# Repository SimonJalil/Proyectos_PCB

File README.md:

# Proyectos_PCB
En este repositorio se encuentran algunos proyectos relacionados con el diseño de PCB en KICAD

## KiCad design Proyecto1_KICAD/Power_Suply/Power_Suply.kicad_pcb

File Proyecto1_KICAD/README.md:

# Proyecto1_KICAD
Fuente de tension

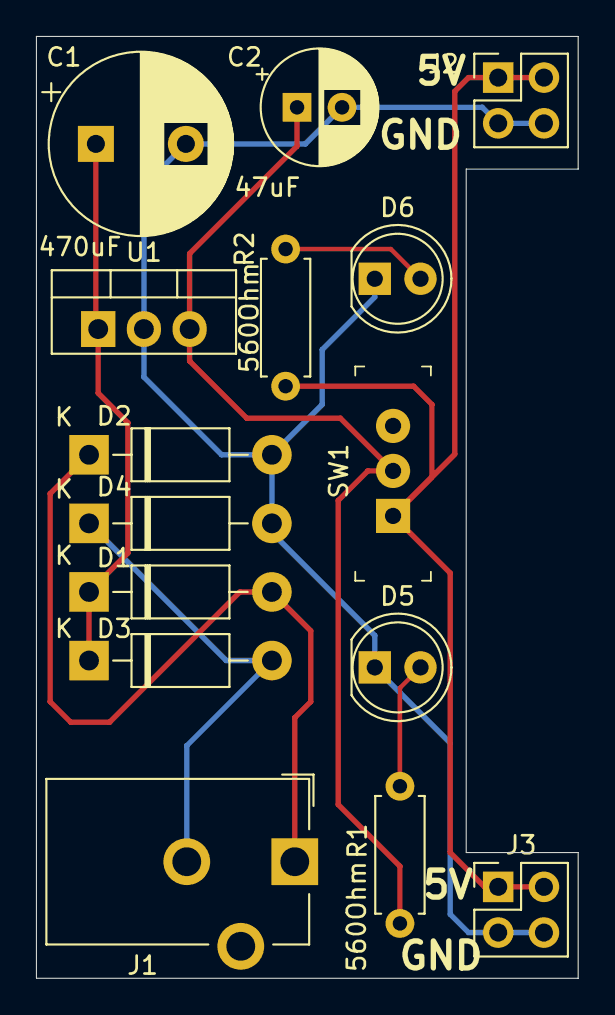
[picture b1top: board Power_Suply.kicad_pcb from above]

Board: 2 copper layers, 30.1 x 52.3 mm, 15 parts (0 on the bottom side), 8 nets.

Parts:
C1: CP; CP_Radial_D10.0mm_P5.00mm
C2: CP; CP_Radial_D6.3mm_P2.50mm
D1, D2, D3, D4: 1N4007; D_DO-41_SOD81_P10.16mm_Horizontal
D5, D6: LED; LED_D5.0mm
J1: Barrel_Jack_Switch; BarrelJack_CUI_PJ-102AH_Horizontal
J2, J3: Conn_02x02_Odd_Even; PinHeader_2x02_P2.54mm_Vertical
R1, R2: R; R_Axial_DIN0207_L6.3mm_D2.5mm_P7.62mm_Horizontal
SW1: SW_DPDT_x2; Switch_Slide_11.6x4mm_EG1218
U1: LM7805_TO220; TO-220-3_Vertical

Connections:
/V-: C1.2, C2.2, D2.2, D4.2, D5.1, D6.1, J2.3, J2.4, J3.3, J3.4, U1.2
/Vin: C1.1, D1.1, D3.1, U1.1
/Vout1: C2.1, R1.1, SW1.2, U1.3
/Vout2: J2.1, J2.2, J3.1, J3.2, R2.1, SW1.1
unnamed: D1.2, D2.1, J1.1
unnamed: D3.2, D4.1, J1.2
unnamed: D5.2, R1.2
unnamed: D6.2, R2.2

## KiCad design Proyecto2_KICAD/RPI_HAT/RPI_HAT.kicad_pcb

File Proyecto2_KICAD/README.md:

# Proyecto2_KICAD
Raspberry Pi HAT

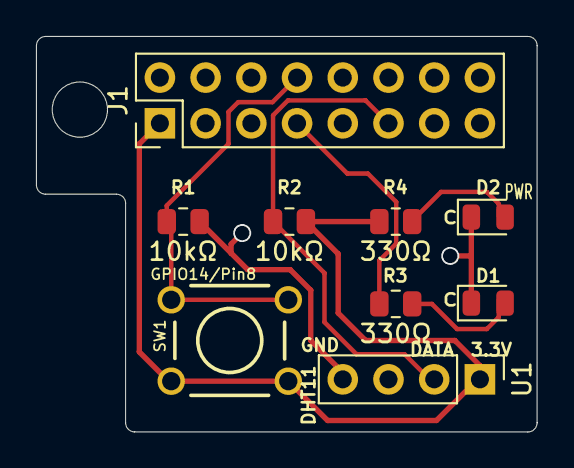
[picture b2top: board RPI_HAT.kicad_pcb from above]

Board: 2 copper layers, 27.8 x 22.0 mm, 9 parts (0 on the bottom side), 7 nets.

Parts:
D1, D2: LED; LED_0805_2012Metric
J1: Raspberry_Pi_2_3; PinHeader_2x08_P2.54mm_Vertical
R1, R2: 10kΩ; R_0805_2012Metric
R3, R4: 330Ω; R_0805_2012Metric
SW1: SW_DPST; SW_PUSHBUTTON_PTH
U1: DHT11; PinHeader_1x04_P2.54mm_Vertical

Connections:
/3V3: J1.1, R2.2, R4.1, SW1.1, U1.1
/button_input: J1.8, R1.1, SW1.2
GND: D1.1, D2.1, J1.6, J1.9, R1.2, U1.4
unnamed: D1.2, R3.2
unnamed: D2.2, R4.2
unnamed: J1.7, R3.1
unnamed: J1.11, R2.1, U1.2

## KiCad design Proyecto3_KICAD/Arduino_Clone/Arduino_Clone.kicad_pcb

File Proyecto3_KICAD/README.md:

# Proyecto3_KICAD
Arduino clone

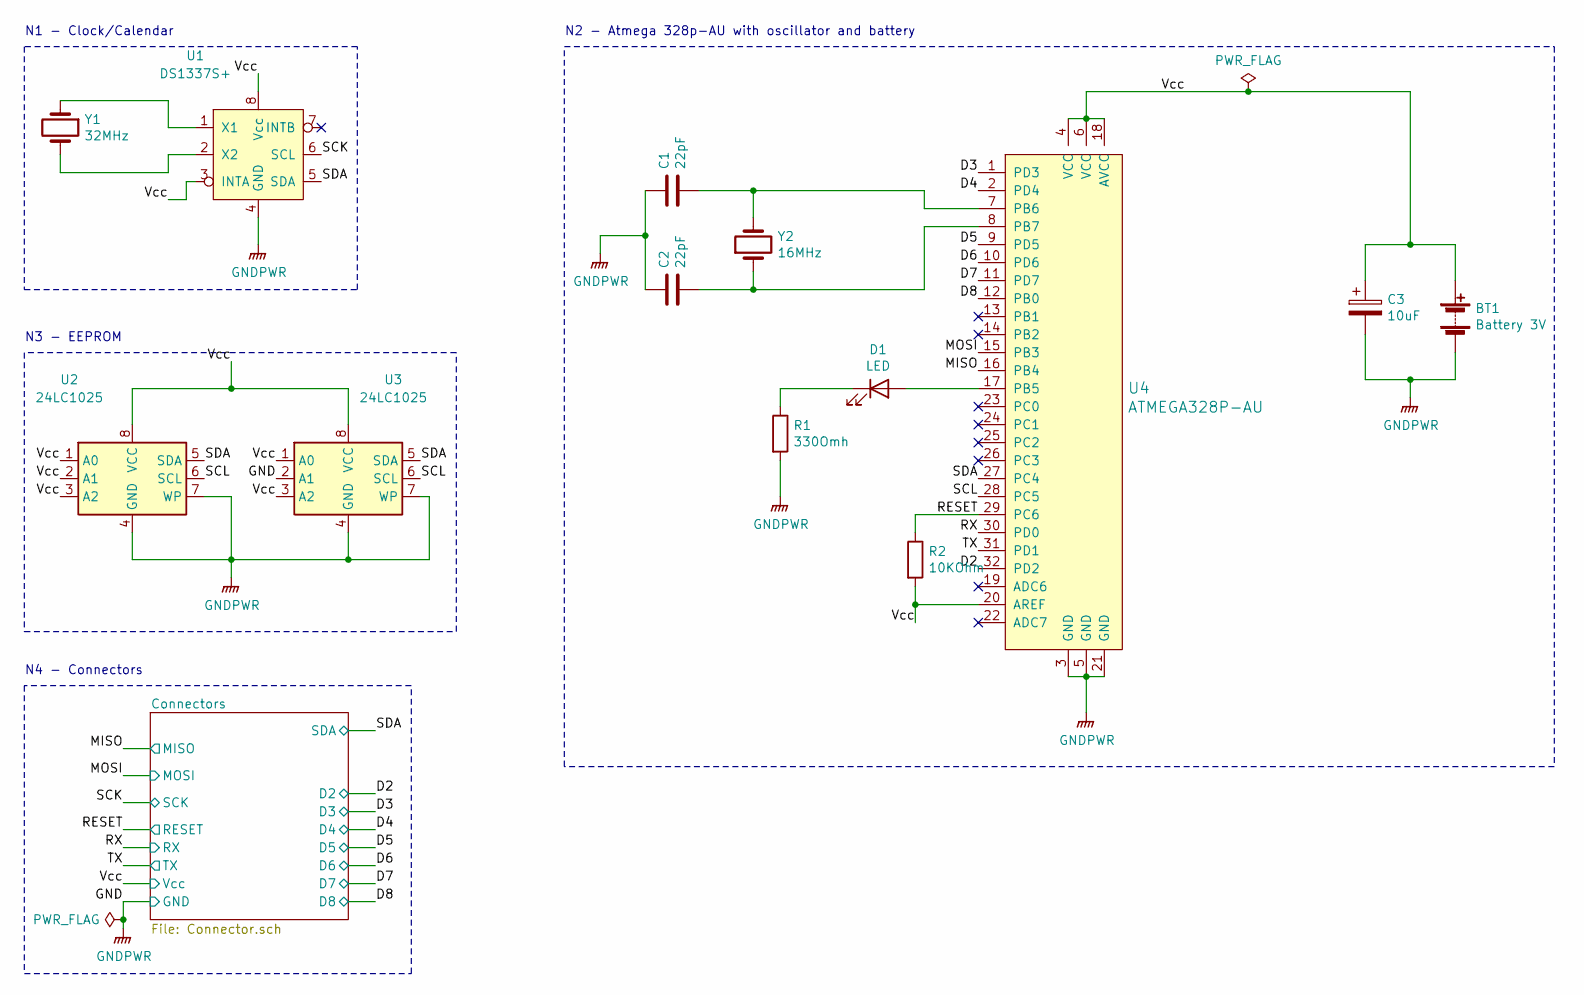
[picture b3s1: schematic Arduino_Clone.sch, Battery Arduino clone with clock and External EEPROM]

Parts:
BT1: Battery 3V; PinHeader_1x02_P2.54mm_Vertical
C1, C2: 22pF; C_0805_2012Metric
C3: 10uF; C_0805_2012Metric
D1: LED; LED_0805_2012Metric_Pad1.15x1.40mm_HandSolder
R1: 330Omh; R_0805_2012Metric
R2: 10KOhm; R_0805_2012Metric
U1: DS1337S+; SO-8_5.3x6.2mm_P1.27mm
U2, U3: 24LC1025; SOIJ-8_5.3x5.3mm_P1.27mm
U4: ATMEGA328P-AU; TQFP-32_7x7mm; MPN ATMEGA328P-AU; Digi-Key_PN ATMEGA328P-AU-ND
Y1: 32MHz; Crystal_SMD_MicroCrystal_CC7V-T1A-2Pin_3.2x1.5mm
Y2: 16MHz; Crystal_SMD_5032-2Pin_5.0x3.2mm_HandSoldering

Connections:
/D2: U4.32 (PD2); also elsewhere on the board
/D3: U4.1 (PD3); also elsewhere on the board
/D4: U4.2 (PD4); also elsewhere on the board
/D5: U4.9 (PD5); also elsewhere on the board
/D6: U4.10 (PD6); also elsewhere on the board
/D7: U4.11 (PD7); also elsewhere on the board
/D8: U4.12 (PB0); also elsewhere on the board
/MISO: U4.16 (PB4); also elsewhere on the board
/MOSI: U4.15 (PB3); also elsewhere on the board
/RESET: R2.1, U4.29 (PC6); also elsewhere on the board
/RX: U4.30 (PD0); also elsewhere on the board
/SCK: U1.6 (SCL); also elsewhere on the board
/SCL: U2.6 (SCL), U3.6 (SCL), U4.28 (PC5)
/SDA: U1.5 (SDA), U2.5 (SDA), U3.5 (SDA), U4.27 (PC4); also elsewhere on the board
/TX: U4.31 (PD1); also elsewhere on the board
/Vcc: BT1.1 (+), C3.1, R2.2, U1.3 (INTA), U1.8 (Vcc), U2.1 (A0), U2.2 (A1), U2.3 (A2), U2.8 (VCC), U3.1 (A0), U3.3 (A2), U3.8 (VCC), U4.4 (VCC), U4.6 (VCC), U4.18 (AVCC), U4.20 (AREF); also elsewhere on the board
GNDPWR: BT1.2 (-), C1.1, C2.1, C3.2, R1.2, U1.4 (GND), U2.4 (GND), U2.7 (WP), U3.2 (A1), U3.4 (GND), U3.7 (WP), U4.3 (GND), U4.5 (GND), U4.21 (GND); also elsewhere on the board
unnamed: C1.2, U4.7 (PB6), Y2.2
unnamed: C2.2, U4.8 (PB7), Y2.1
unnamed: D1.1 (K), R1.1
unnamed: D1.2 (A), U4.17 (PB5)
unnamed: U1.1 (X1), Y1.1
unnamed: U1.2 (X2), Y1.2

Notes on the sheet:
N1 - Clock/Calendar
N3 - EEPROM
N2 - Atmega 328p-AU with oscillator and battery
N4 - Connectors

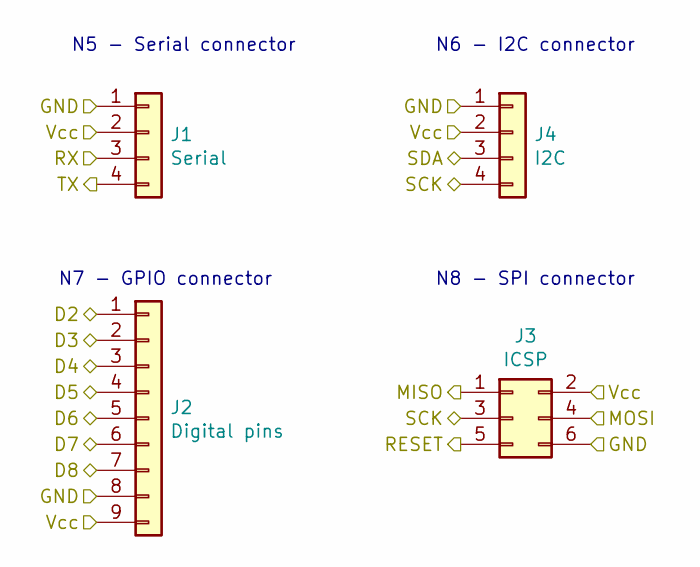
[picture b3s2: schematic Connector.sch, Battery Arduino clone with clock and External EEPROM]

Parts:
J1: Serial; PinSocket_1x04_P2.54mm_Vertical
J2: Digital pins; PinSocket_1x09_P2.54mm_Vertical
J3: ICSP; PinSocket_2x03_P2.54mm_Vertical
J4: I2C; PinSocket_1x04_P2.54mm_Vertical

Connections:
/D2: J2.1; also elsewhere on the board
/D3: J2.2; also elsewhere on the board
/D4: J2.3; also elsewhere on the board
/D5: J2.4; also elsewhere on the board
/D6: J2.5; also elsewhere on the board
/D7: J2.6; also elsewhere on the board
/D8: J2.7; also elsewhere on the board
/MISO: J3.1; also elsewhere on the board
/MOSI: J3.4; also elsewhere on the board
/RESET: J3.5; also elsewhere on the board
/RX: J1.3; also elsewhere on the board
/SCK: J3.3, J4.4; also elsewhere on the board
/SDA: J4.3; also elsewhere on the board
/TX: J1.4; also elsewhere on the board
/Vcc: J1.2, J2.9, J3.2, J4.2; also elsewhere on the board
GNDPWR: J1.1, J2.8, J3.6, J4.1; also elsewhere on the board

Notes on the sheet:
N5 - Serial connector
N6 - I2C connector
N7 - GPIO connector
N8 - SPI connector

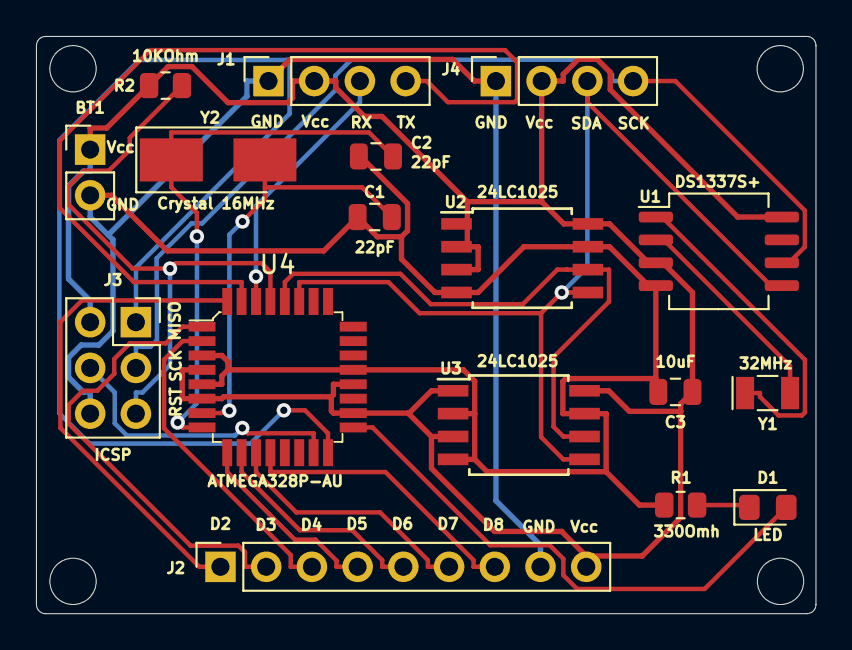
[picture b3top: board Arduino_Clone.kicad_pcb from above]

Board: 2 copper layers, 43.3 x 32.1 mm, 17 parts (0 on the bottom side), 23 nets.

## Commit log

2021-09-04 Seguimiento de Proyectos en KICAD
